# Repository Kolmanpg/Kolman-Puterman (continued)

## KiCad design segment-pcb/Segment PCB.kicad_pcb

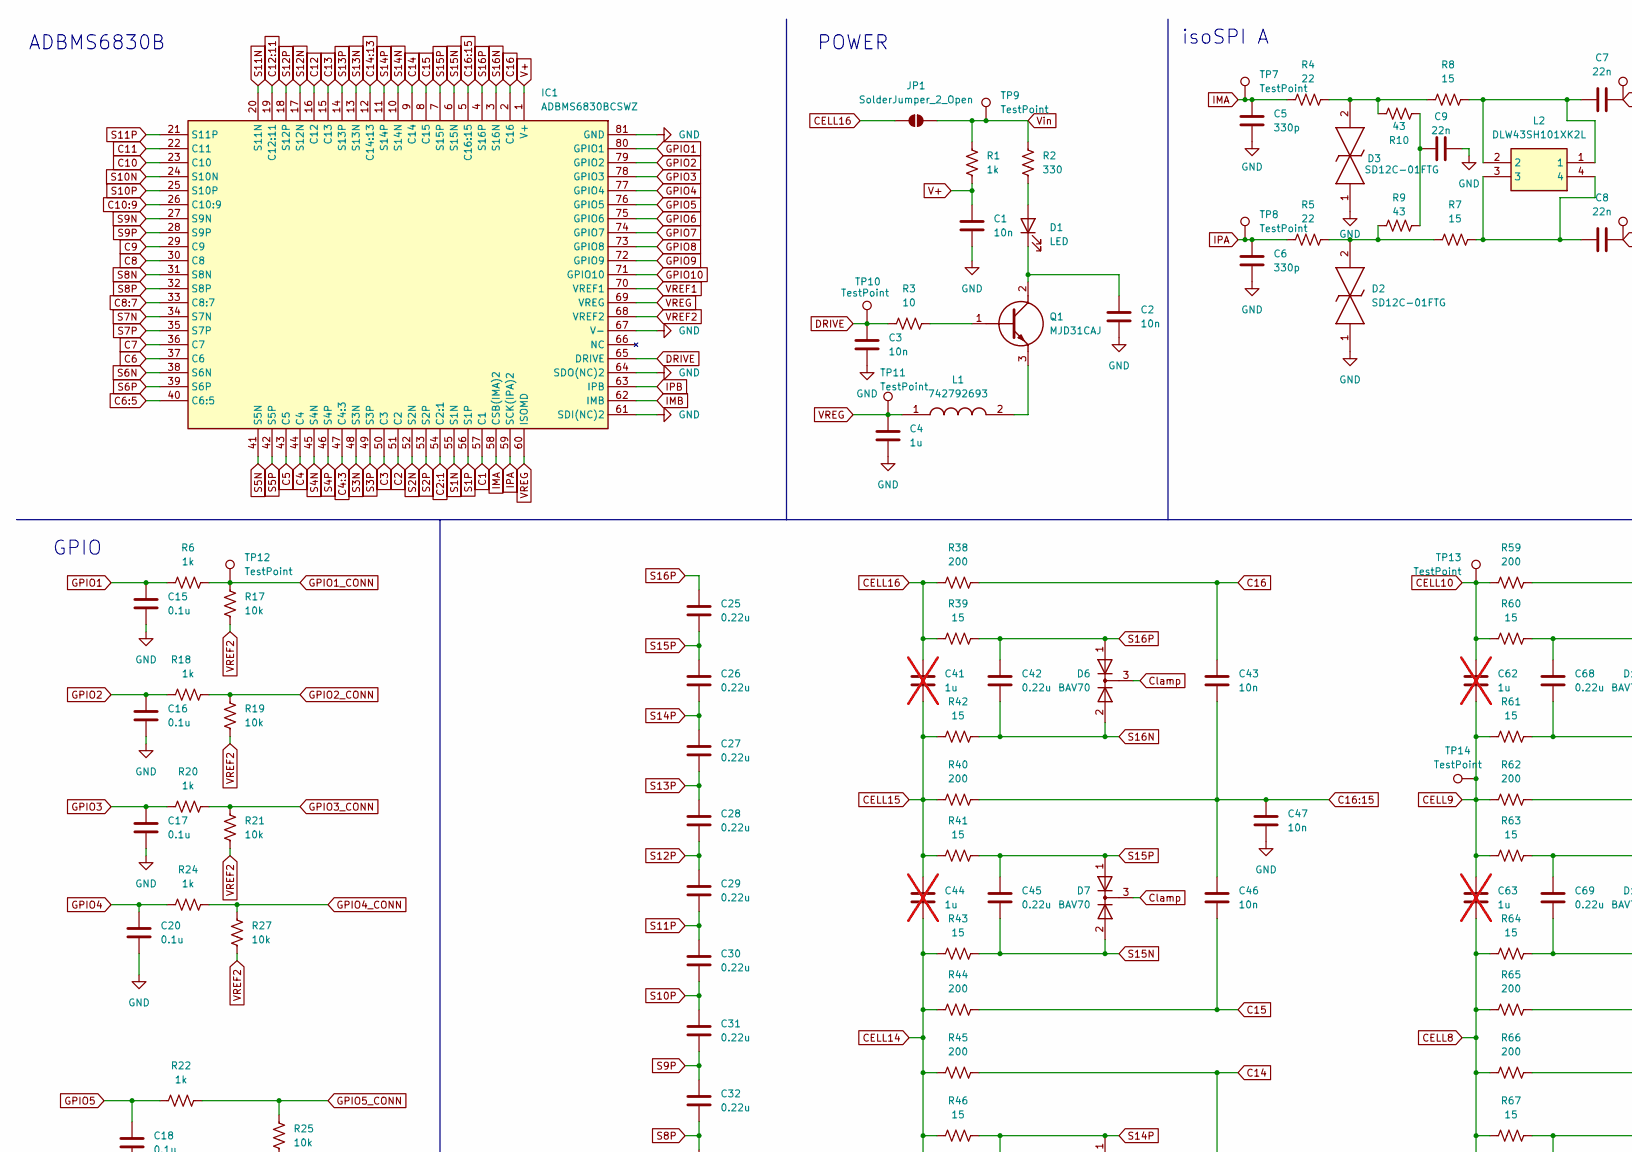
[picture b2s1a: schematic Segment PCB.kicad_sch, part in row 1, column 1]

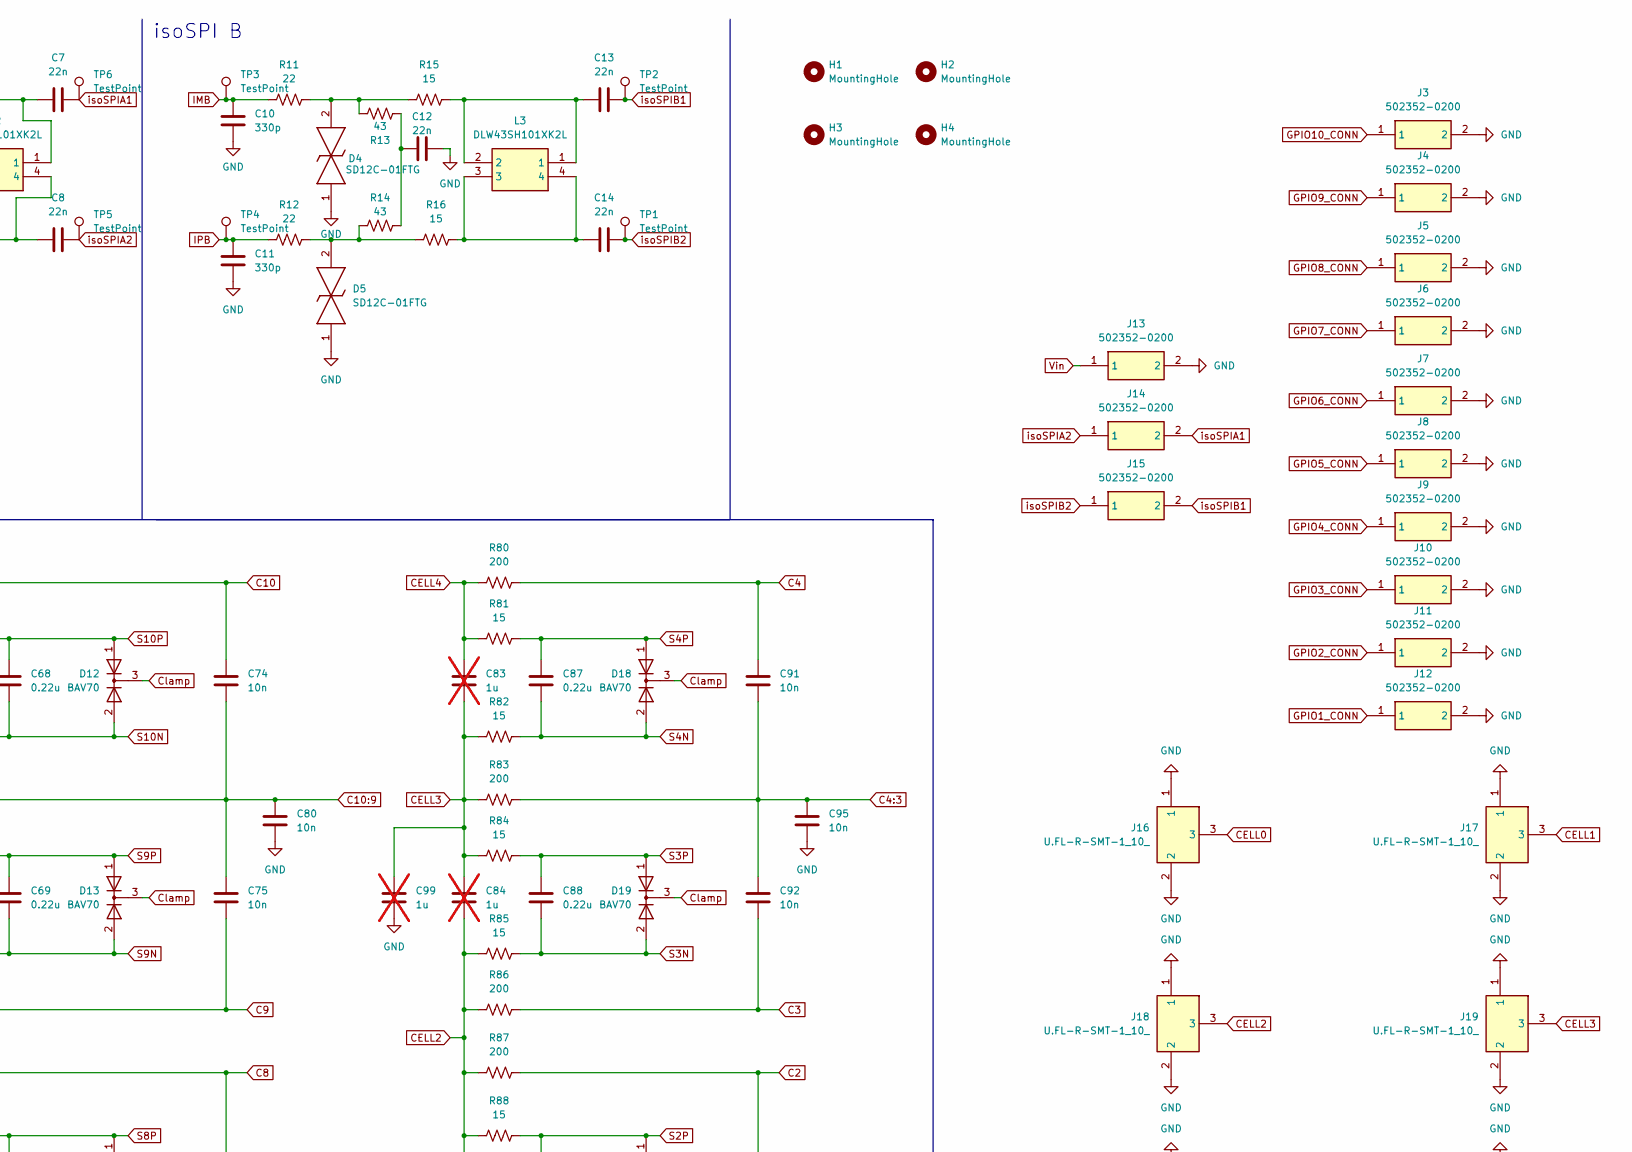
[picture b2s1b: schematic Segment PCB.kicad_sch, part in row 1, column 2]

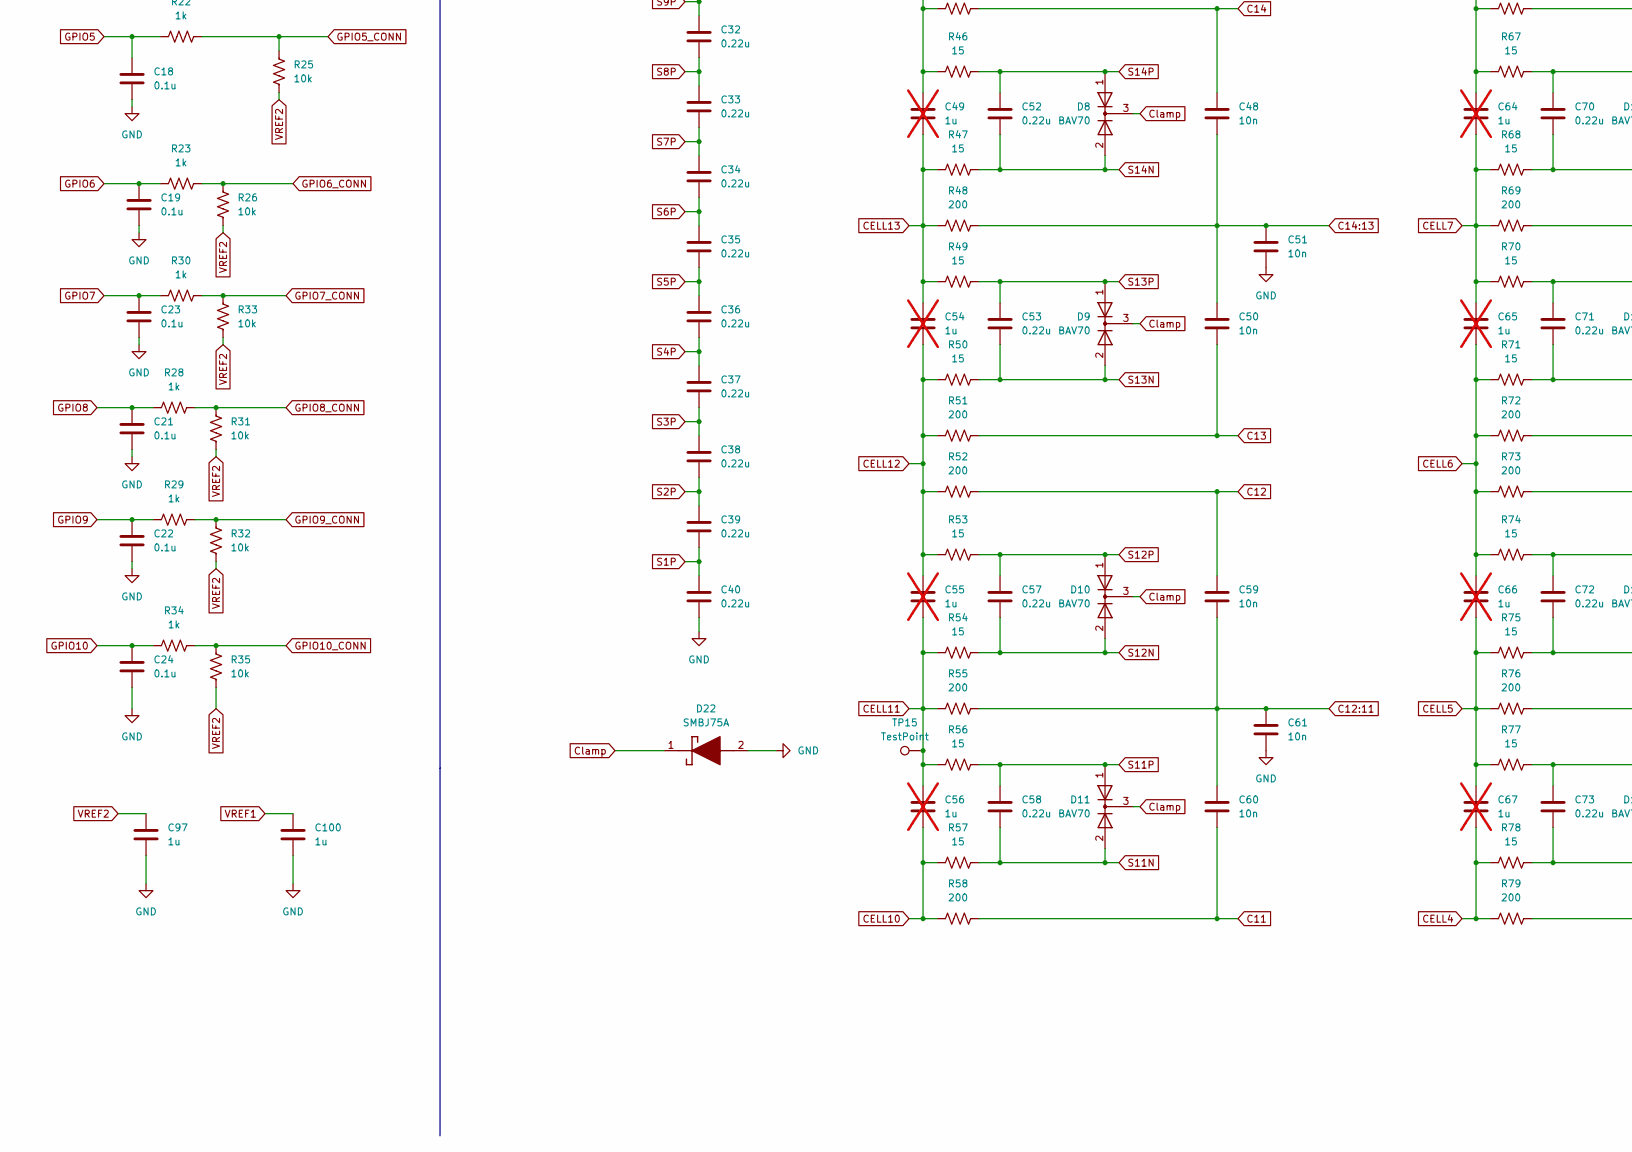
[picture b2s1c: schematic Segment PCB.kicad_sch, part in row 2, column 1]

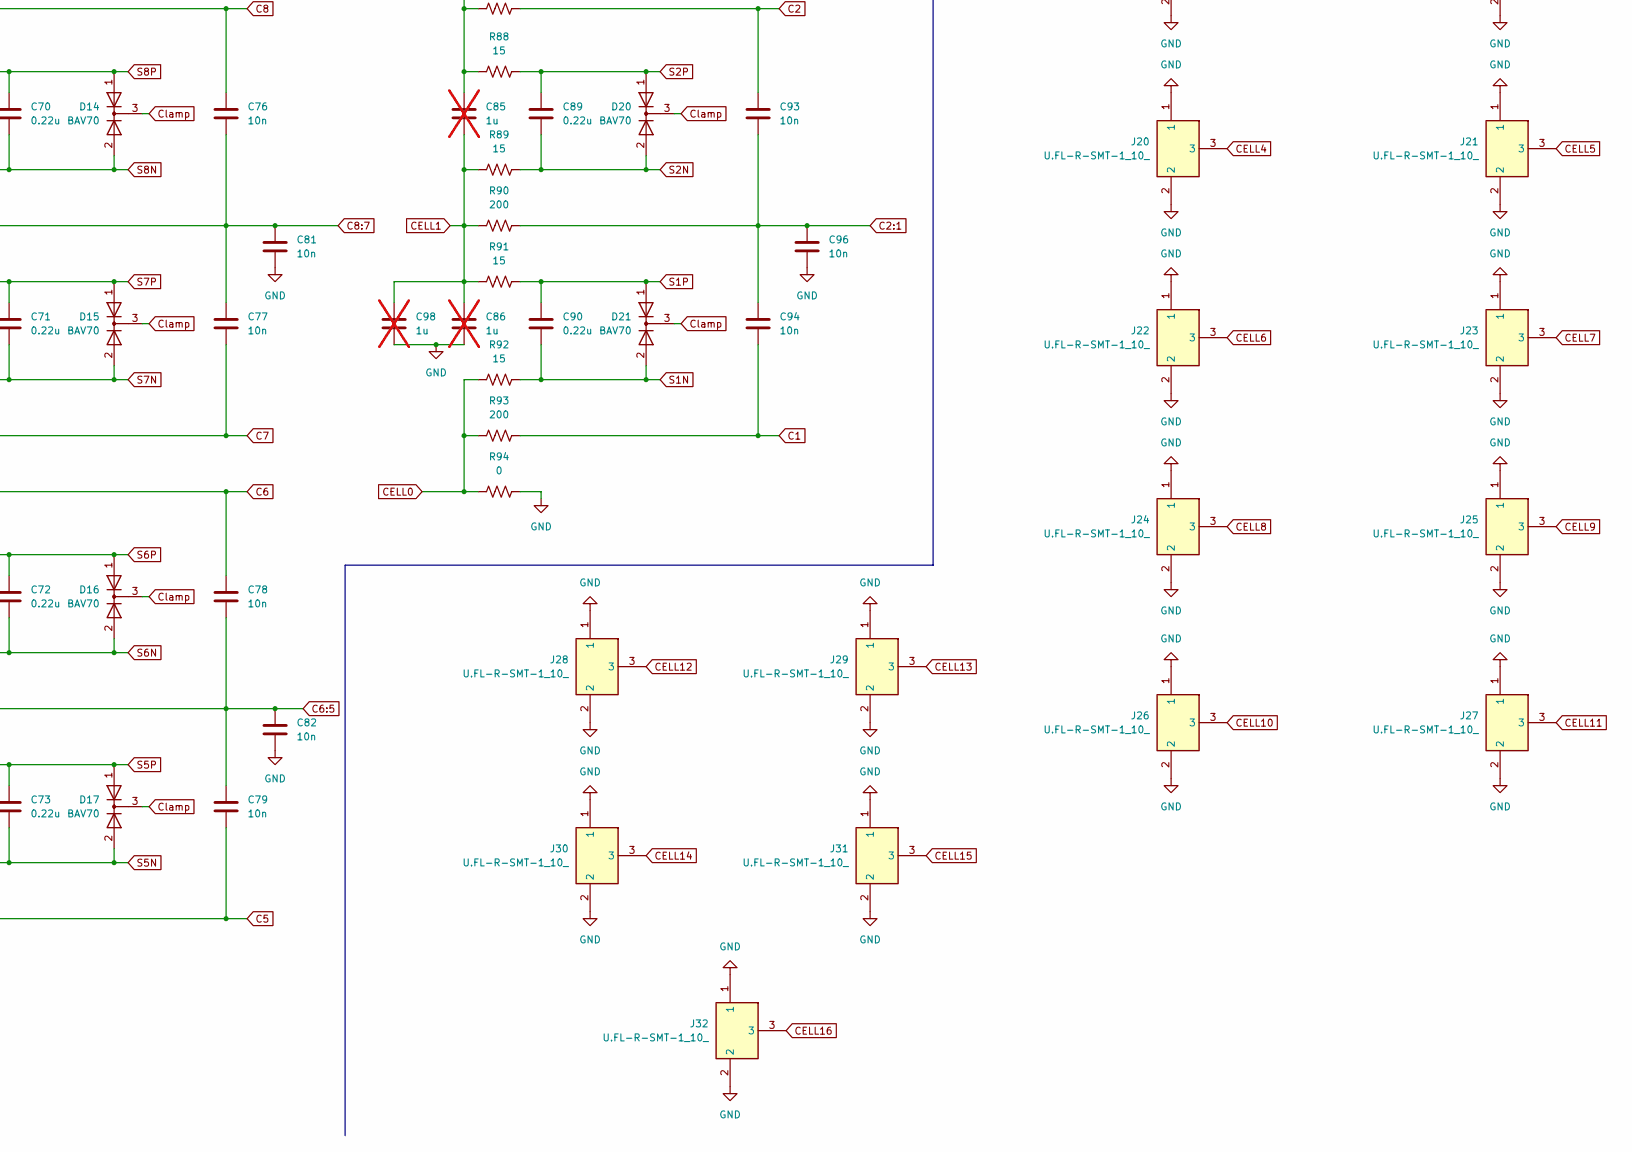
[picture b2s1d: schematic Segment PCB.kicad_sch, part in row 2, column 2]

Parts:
C1, C2, C3, C43, C46, C47, C48, C50, C51, C59, C60, C61, C74, C75, C76, C77, C78, C79, C80, C81, C82, C91, C92, C93, C94, C95, C96: 10n; C_0805_2012Metric_Pad1.18x1.45mm_HandSolder; Manufacturer_Part_Number CL21B103KBANNNC; JLCPCB C1710
C4, C97, C100: 1u; C_0805_2012Metric_Pad1.18x1.45mm_HandSolder; Manufacturer_Part_Number CL21B105KBFNNNE; JLCPCB C28323
C5, C6, C10, C11: 330p; C_0805_2012Metric_Pad1.18x1.45mm_HandSolder
C7, C8, C9, C12, C13, C14: 22n; C_0805_2012Metric_Pad1.18x1.45mm_HandSolder; Manufacturer_Part_Number CL21B223KBANNNC; JLCPCB C1729
C15, C16, C17, C18, C19, C20, C21, C22, C23, C24: 0.1u; C_0805_2012Metric_Pad1.18x1.45mm_HandSolder; Manufacturer_Part_Number CL21B104KCFNNNE; JLCPCB C28233
C25, C26, C27, C28, C29, C30, C31, C32, C33, C34, C35, C36, C37, C38, C39, C40, C42, C45, C52, C53, C57, C58, C68, C69, C70, C71, C72, C73, C87, C88, C89, C90: 0.22u; C_0805_2012Metric_Pad1.18x1.45mm_HandSolder; Manufacturer_Part_Number CL21B224KBFNNNE; JLCPCB C5378
C41, C44, C49, C54, C55, C56, C62, C63, C64, C65, C66, C67, C83, C84, C85, C86, C98, C99: 1u; C_0805_2012Metric_Pad1.18x1.45mm_HandSolder; Manufacturer_Part_Number CL21B105KBFNNNE; JLCPCB C28323; not fitted
D1: LED; LED_0805_2012Metric_Pad1.15x1.40mm_HandSolder; Manufacturer_Part_Number KT-0805G; JLCPCB C2297
D2, D3, D4, D5: SD12C-01FTG; SOD2613X114N; Mouser Part Number 576-SD12C-01FTG
D6, D7, D8, D9, D10, D11, D12, D13, D14, D15, D16, D17, D18, D19, D20, D21: BAV70; SOT-23; Manufacturer_Part_Number BAV70; JLCPCB C68978
D22: SMBJ75A; Mouser Part Number 750-CDBB3200-HF
H1, H2, H3, H4: MountingHole; MountingHole_3mm
IC1: ADBMS6830BCSWZ; QFP50P1400X1400X160-81N; Mouser Part Number 584-ADBMS6830BCSWZ
J3, J4, J5, J6, J7, J8, J9, J10, J11, J12, J13, J14, J15: 502352-0200; 5023520200; Mouser Part Number 538-502352-0200
J16, J17, J18, J19, J20, J21, J22, J23, J24, J25, J26, J27, J28, J29, J30, J31, J32: U.FL-R-SMT-1_10_; Mouser Part Number 798-U.FL-R-SMT-110
JP1: SolderJumper_2_Open; SolderJumper-2_P1.3mm_Open_RoundedPad1.0x1.5mm
L1: 742792693; INDC1608X100N; Mouser Part Number 710-742792693
L2, L3: DLW43SH101XK2L; Mouser Part Number 81-DLW43SH101XK2L
Q1: MJD31CAJ; Mouser Part Number 771-MJD31CAJ
R1, R6, R18, R20, R22, R23, R24, R28, R29, R30, R34: 1k; R_0805_2012Metric_Pad1.20x1.40mm_HandSolder; Manufacturer_Part_Number 0805W8F1001T5E; JLCPCB C17513
R2: 330; R_0805_2012Metric_Pad1.20x1.40mm_HandSolder; Manufacturer_Part_Number 0805W8F3300T5E; JLCPCB C17630
R3: 10; R_0805_2012Metric_Pad1.20x1.40mm_HandSolder; Manufacturer_Part_Number 0805W8F100JT5E; JLCPCB C17415
R4, R5, R11, R12: 22; R_0805_2012Metric_Pad1.20x1.40mm_HandSolder; Manufacturer_Part_Number 0805W8F220JT5E; JLCPCB C17561
R7, R8, R15, R16: 15; R_0805_2012Metric_Pad1.20x1.40mm_HandSolder
R9, R10, R13, R14: 43; R_0805_2012Metric_Pad1.20x1.40mm_HandSolder
R17, R19, R21, R25, R26, R27, R31, R32, R33, R35: 10k; R_0805_2012Metric_Pad1.20x1.40mm_HandSolder; Manufacturer_Part_Number 0805W8F1002T5E; JLCPCB C17414
R38, R40, R44, R45, R48, R51, R52, R55, R58, R59, R62, R65, R66, R69, R72, R73, R76, R79, R80, R83, R86, R87, R90, R93: 200; R_0805_2012Metric_Pad1.20x1.40mm_HandSolder; Manufacturer_Part_Number 0805W8F2000T5E; JLCPCB C17540
R39, R41, R42, R43, R46, R47, R49, R50, R53, R54, R56, R57, R60, R61, R63, R64, R67, R68, R70, R71, R74, R75, R77, R78, R81, R82, R84, R85, R88, R89, R91, R92: 15; RESC6432X65N; Manufacturer_Part_Number 352115RFT
R94: 0; R_0805_2012Metric_Pad1.20x1.40mm_HandSolder; Manufacturer_Part_Number 0805W8F0000T5E; JLCPCB C17477
TP1, TP2, TP3, TP4, TP5, TP6, TP7, TP8, TP9, TP10, TP11, TP12, TP13, TP14, TP15: TestPoint; TestPoint_Pad_D1.0mm

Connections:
C1: C94.2, IC1.57 (C1), R93.2
C2: C93.1, IC1.51 (C2), R87.2
C2:1: C93.2, C94.1, C96.1, IC1.54 (C2:1), R90.2
C3: C92.2, IC1.50 (C3), R86.2
C4: C91.1, IC1.44 (C4), R80.2
C4:3: C91.2, C92.1, C95.1, IC1.47 (C4:3), R83.2
C5: C79.2, IC1.43 (C5), R79.2
C6: C78.1, IC1.37 (C6), R73.2
C6:5: C78.2, C79.1, C82.1, IC1.40 (C6:5), R76.2
C7: C77.2, IC1.36 (C7), R72.2
C8: C76.1, IC1.30 (C8), R66.2
C8:7: C76.2, C77.1, C81.1, IC1.33 (C8:7), R69.2
C9: C75.2, IC1.29 (C9), R65.2
C10: C74.1, IC1.23 (C10), R59.2
C10:9: C74.2, C75.1, C80.1, IC1.26 (C10:9), R62.2
C11: C60.2, IC1.22 (C11), R58.2
C12: C59.1, IC1.16 (C12), R52.2
C12:11: C59.2, C60.1, C61.1, IC1.19 (C12:11), R55.2
C13: C50.2, IC1.15 (C13), R51.2
C14: C48.1, IC1.9 (C14), R45.2
C14:13: C48.2, C50.1, C51.1, IC1.12 (C14:13), R48.2
C15: C46.2, IC1.8 (C15), R44.2
C16: C43.1, IC1.2 (C16), R38.2
C16:15: C43.2, C46.1, C47.1, IC1.5 (C16:15), R40.2
CELL0: J16.3, R92.1, R93.1, R94.1
CELL1: C85.2, C86.1, C98.1, J17.3, R89.1, R90.1, R91.1
CELL2: C84.2, C85.1, J18.3, R85.1, R86.1, R87.1, R88.1
CELL3: C83.2, C84.1, C99.1, J19.3, R82.1, R83.1, R84.1
CELL4: C67.2, C83.1, J20.3, R78.1, R79.1, R80.1, R81.1
CELL5: C66.2, C67.1, J21.3, R75.1, R76.1, R77.1
CELL6: C65.2, C66.1, J22.3, R71.1, R72.1, R73.1, R74.1
CELL7: C64.2, C65.1, J23.3, R68.1, R69.1, R70.1
CELL8: C63.2, C64.1, J24.3, R64.1, R65.1, R66.1, R67.1
CELL9: C62.2, C63.1, J25.3, R61.1, R62.1, R63.1, TP14.1
CELL10: C56.2, C62.1, J26.3, R57.1, R58.1, R59.1, R60.1, TP13.1
CELL11: C55.2, C56.1, J27.3, R54.1, R55.1, R56.1, TP15.1
CELL12: C54.2, C55.1, J28.3, R50.1, R51.1, R52.1, R53.1
CELL13: C49.2, C54.1, J29.3, R47.1, R48.1, R49.1
CELL14: C44.2, C49.1, J30.3, R43.1, R44.1, R45.1, R46.1
CELL15: C41.2, C44.1, J31.3, R40.1, R41.1, R42.1
CELL16: C41.1, J32.3, JP1.1 (A), R38.1, R39.1
Clamp: D6.3 (K), D7.3 (K), D8.3 (K), D9.3 (K), D10.3 (K), D11.3 (K), D12.3 (K), D13.3 (K), D14.3 (K), D15.3 (K), D16.3 (K), D17.3 (K), D18.3 (K), D19.3 (K), D20.3 (K), D21.3 (K), D22.1 (K)
DRIVE: C3.1, IC1.65 (DRIVE), R3.1, TP10.1
GND: C1.2, C2.2, C3.2, C4.2, C5.2, C6.2, C9.2, C10.2, C11.2, C12.2, C15.2, C16.2, C17.2, C18.2, C19.2, C20.2, C21.2, C22.2, C23.2, C24.2, C40.2, C47.2, C51.2, C61.2, C80.2, C81.2, C82.2, C86.2, C95.2, C96.2, C97.2, C98.2, C99.2, C100.2, D2.1, D3.1, D4.1, D5.1, D22.2 (A), IC1.61 (SDI(NC)2), IC1.64 (SDO(NC)2), IC1.67 (V-), IC1.81 (GND), J3.2, J4.2, J5.2, J6.2, J7.2, J8.2, J9.2, J10.2, J11.2, J12.2, J13.2, J16.1, J16.2, J17.1, J17.2, J18.1, J18.2, J19.1, J19.2, J20.1, J20.2, J21.1, J21.2, J22.1, J22.2, J23.1, J23.2, J24.1, J24.2, J25.1, J25.2, J26.1, J26.2, J27.1, J27.2, J28.1, J28.2, J29.1, J29.2, J30.1, J30.2, J31.1, J31.2, J32.1, J32.2, R94.2
GPIO1: C15.1, IC1.80 (GPIO1), R6.1
GPIO1_CONN: J12.1, R6.2, R17.2, TP12.1
GPIO2: C16.1, IC1.79 (GPIO2), R18.1
GPIO2_CONN: J11.1, R18.2, R19.2
GPIO3: C17.1, IC1.78 (GPIO3), R20.1
GPIO3_CONN: J10.1, R20.2, R21.2
GPIO4: C20.1, IC1.77 (GPIO4), R24.1
GPIO4_CONN: J9.1, R24.2, R27.2
GPIO5: C18.1, IC1.76 (GPIO5), R22.1
GPIO5_CONN: J8.1, R22.2, R25.2
GPIO6: C19.1, IC1.75 (GPIO6), R23.1
GPIO6_CONN: J7.1, R23.2, R26.2
GPIO7: C23.1, IC1.74 (GPIO7), R30.1
GPIO7_CONN: J6.1, R30.2, R33.2
GPIO8: C21.1, IC1.73 (GPIO8), R28.1
GPIO8_CONN: J5.1, R28.2, R31.2
GPIO9: C22.1, IC1.72 (GPIO9), R29.1
GPIO9_CONN: J4.1, R29.2, R32.2
GPIO10: C24.1, IC1.71 (GPIO10), R34.1
GPIO10_CONN: J3.1, R34.2, R35.2
IMA: C5.1, IC1.58 (CSB(IMA)2), R4.1, TP7.1
IMB: C10.1, IC1.62 (IMB), R11.1, TP3.1
IPA: C6.1, IC1.59 (SCK(IPA)2), R5.1, TP8.1
IPB: C11.1, IC1.63 (IPB), R12.1, TP4.1
unnamed: C7.1, L2.1, L2.2, R8.2
unnamed: C8.1, L2.3, L2.4, R7.2
unnamed: C9.1, R9.2, R10.1
unnamed: C12.1, R13.1, R14.2
unnamed: C13.1, L3.1, L3.2, R15.2
unnamed: C14.1, L3.3, L3.4, R16.2
unnamed: D1.2 (A), R2.2
unnamed: C2.1, D1.1 (K), Q1.2 (C)
unnamed: D2.2, R5.2, R7.1, R9.1
unnamed: D3.2, R4.2, R8.1, R10.2
unnamed: D4.2, R11.2, R13.2, R15.1
unnamed: D5.2, R12.2, R14.1, R16.1
unnamed: Q1.1 (B), R3.2
unnamed: L1.2, Q1.3 (E)
S1N: C90.2, D21.2 (A), IC1.55 (S1N), R92.2
S1P: C39.2, C40.1, C90.1, D21.1 (A), IC1.56 (S1P), R91.2
S2N: C89.2, D20.2 (A), IC1.52 (S2N), R89.2
S2P: C38.2, C39.1, C89.1, D20.1 (A), IC1.53 (S2P), R88.2
S3N: C88.2, D19.2 (A), IC1.48 (S3N), R85.2
S3P: C37.2, C38.1, C88.1, D19.1 (A), IC1.49 (S3P), R84.2
S4N: C87.2, D18.2 (A), IC1.45 (S4N), R82.2
S4P: C36.2, C37.1, C87.1, D18.1 (A), IC1.46 (S4P), R81.2
S5N: C73.2, D17.2 (A), IC1.41 (S5N), R78.2
S5P: C35.2, C36.1, C73.1, D17.1 (A), IC1.42 (S5P), R77.2
S6N: C72.2, D16.2 (A), IC1.38 (S6N), R75.2
S6P: C34.2, C35.1, C72.1, D16.1 (A), IC1.39 (S6P), R74.2
S7N: C71.2, D15.2 (A), IC1.34 (S7N), R71.2
S7P: C33.2, C34.1, C71.1, D15.1 (A), IC1.35 (S7P), R70.2
S8N: C70.2, D14.2 (A), IC1.31 (S8N), R68.2
S8P: C32.2, C33.1, C70.1, D14.1 (A), IC1.32 (S8P), R67.2
S9N: C69.2, D13.2 (A), IC1.27 (S9N), R64.2
S9P: C31.2, C32.1, C69.1, D13.1 (A), IC1.28 (S9P), R63.2
S10N: C68.2, D12.2 (A), IC1.24 (S10N), R61.2
S10P: C30.2, C31.1, C68.1, D12.1 (A), IC1.25 (S10P), R60.2
S11N: C58.2, D11.2 (A), IC1.20 (S11N), R57.2
S11P: C29.2, C30.1, C58.1, D11.1 (A), IC1.21 (S11P), R56.2
S12N: C57.2, D10.2 (A), IC1.17 (S12N), R54.2
S12P: C28.2, C29.1, C57.1, D10.1 (A), IC1.18 (S12P), R53.2
S13N: C53.2, D9.2 (A), IC1.13 (S13N), R50.2
S13P: C27.2, C28.1, C53.1, D9.1 (A), IC1.14 (S13P), R49.2
S14N: C52.2, D8.2 (A), IC1.10 (S14N), R47.2
S14P: C26.2, C27.1, C52.1, D8.1 (A), IC1.11 (S14P), R46.2
S15N: C45.2, D7.2 (A), IC1.6 (S15N), R43.2
S15P: C25.2, C26.1, C45.1, D7.1 (A), IC1.7 (S15P), R41.2
S16N: C42.2, D6.2 (A), IC1.3 (S16N), R42.2
S16P: C25.1, C42.1, D6.1 (A), IC1.4 (S16P), R39.2
V+: C1.1, IC1.1 (V+), R1.2
VREF1: C100.1, IC1.70 (VREF1)
VREF2: C97.1, IC1.68 (VREF2), R17.1, R19.1, R21.1, R25.1, R26.1, R27.1, R31.1, R32.1, R33.1, R35.1
VREG: C4.1, IC1.60 (ISOMD), IC1.69 (VREG), L1.1, TP11.1
Vin: J13.1, JP1.2 (B), R1.1, R2.1, TP9.1
isoSPIA1: C7.2, J14.2, TP6.1
isoSPIA2: C8.2, J14.1, TP5.1
isoSPIB1: C13.2, J15.2, TP2.1
isoSPIB2: C14.2, J15.1, TP1.1

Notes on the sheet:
POWER
isoSPI A
ADBMS6830B
GPIO
isoSPI B

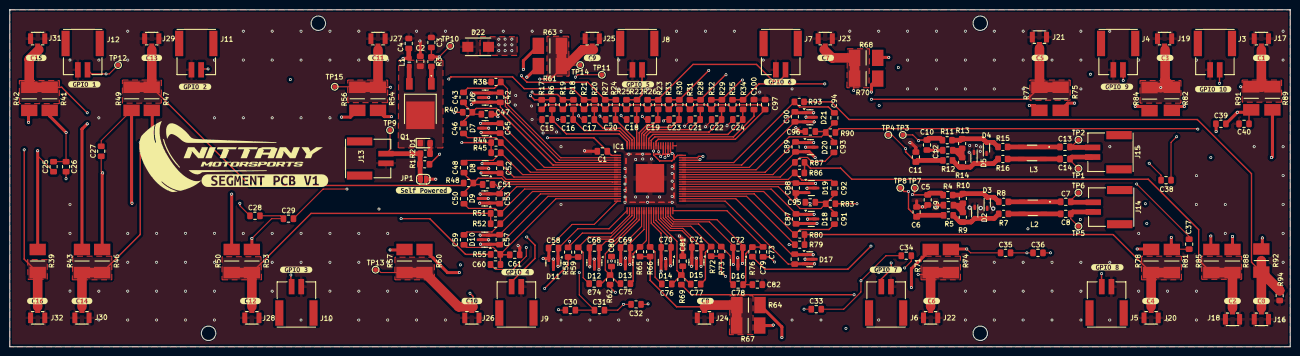
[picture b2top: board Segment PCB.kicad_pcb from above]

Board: 4 copper layers, 266.0 x 70.0 mm, 281 parts (1 on the bottom side), 123 nets.

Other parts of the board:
kibuzzard-671AD0BD: G***; kibuzzard-671AD0BD
kibuzzard-671AD1D4: G***; kibuzzard-671AD1D4
kibuzzard-671AD1D9: G***; kibuzzard-671AD1D9
kibuzzard-671AD1E8: G***; kibuzzard-671AD1E8
kibuzzard-671AD1F8: G***; kibuzzard-671AD1F8
kibuzzard-671AD4A2: G***; kibuzzard-671AD4A2
kibuzzard-671AD4AD: G***; kibuzzard-671AD4AD
kibuzzard-671AD4C0: G***; kibuzzard-671AD4C0
kibuzzard-671AD4CD: G***; kibuzzard-671AD4CD
kibuzzard-671AD11F: G***; kibuzzard-671AD11F
kibuzzard-671AD12D: G***; kibuzzard-671AD12D
kibuzzard-671AD13E: G***; kibuzzard-671AD13E
kibuzzard-671AD21F: G***; kibuzzard-671AD21F
kibuzzard-671AD22C: G***; kibuzzard-671AD22C
kibuzzard-671AD51B: G***; kibuzzard-671AD51B
kibuzzard-671AD110: G***; kibuzzard-671AD110
kibuzzard-671AD135: G***; kibuzzard-671AD135
kibuzzard-671AD147: G***; kibuzzard-671AD147
kibuzzard-671AD153: G***; kibuzzard-671AD153
kibuzzard-671AD205: G***; kibuzzard-671AD205
kibuzzard-671AD211: G***; kibuzzard-671AD211
kibuzzard-671AD218: G***; kibuzzard-671AD218
kibuzzard-671AD462: G***; kibuzzard-671AD462
kibuzzard-671AD496: G***; kibuzzard-671AD496
kibuzzard-671AD506: G***; kibuzzard-671AD506
kibuzzard-671AD523: G***; kibuzzard-671AD523
kibuzzard-671AD529: G***; kibuzzard-671AD529
kibuzzard-671ADAE7: G***; kibuzzard-671ADAE7
kibuzzard-671ADDD3: G***; kibuzzard-671ADDD3
kibuzzard-671ADE02: G***; kibuzzard-671ADE02
